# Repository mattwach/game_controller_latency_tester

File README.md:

# game_controller_latency_tester

This project provides a (couple of) hardware designs for interfacing a game
controller to a Raspberry PI (or similar) and automatically measuring the input
latency added by the controller.

## What is input latency?

The "input latency" I'm referring to in this document is the amount of time
that passes between a button being pressed on the controller and application
(game) receiving the event.

This is the sum of all of the following:

   1. The game controller hardware signaling that the button is pressed
      (very fast)
   2. The game controller firmware processing this signal into a USB or
      bluetooth message (varies)
   3. The Raspberry PI USB/bluetooth hardware receiving the message and notifying the
      OS (usually fast)
   4. The Raspberry PI OS handling the message and passing it forward to
      the application (usually fast)

> "button" could also mean deflecting a stick.

## Raspberry PI verses Microcontroller Test Setup

Some setups, such as [this one](https://inputlag.science/controller/methodology)
use microcontroller hardware to handle #1, #3 and #4.  This project uses a
Raspberry PI instead.

One reason to use a microcontroller is more control over the environment.  A
Raspberry PI running Linux could get interrupted in the middle of a measurement
which would unfairly penalize the result.  That said, the PI has many
advantages as well:

   1. Even though the Raspberry PI *could* get interrupted, it's fairly simple
      to create a environment where this is not likely to happen.  For example
      you could run without a graphical environment or any services.  My own
      tests didn't even bother being careful with this and still got similar
      results as the [microcontroller version](https://inputlag.science/controller/methodology)
      testing the < 1ms [GP2040](https://github.com/FeralAI/GP2040) firmware.
   2. The Raspberry PI could be argued a more relevant test in some respects
      as it's using the same path that [RetroPie](https://retropie.org.uk/) would use.
   3. Supporting different configurations is much easier with Raspberry PI.
      For example, testing a bluetooth-based controller generally requires no
      additional hardware or setup.

## Other hardware options.

If Raspberry PI's are still hard to find, there are many alternative options.
The needed requirements are GPIO support and USB.  You *could* use a generic
PC with a USB to GPIO converter to send the needed trigger signals.  Something
like [this](https://www.adafruit.com/product/2264) or make-your-own with a PI Pico.

> Not using a Raspberry pi will likely require some tweaks to the
> source code provided in this project.

So in the text below, you can replace "Raspberry PI" with whatever you hapen to be using.

## Process Overview

   1. The Raspberry PI toggles a GPIO and notes the current time in microsecond
      resolution.
   2. The GPIO signals the game controller to sense that a button was pressed (or
      a stick was deflected)
   3. The controller sends a corresponding USB/Bluetooth message back to the
      Raspberry PI.
   4. Upon receiving the USB/Bluetooth message, the Raspberry PI notes how much
      time has passed since sending the GPIO

1-4 repeats many time (1000 or more) to build up statistics.

## Test Pattern

One test pattern would be to toggle the GPIOs very fast, like 1000 times per
second.  But since no human player could ever do this, it could be argued that
poor results in these setups might not be represent a real-world experience.

The test programs in this project try to set up a more "real world" situation
but toggling two GPIO channels at 10Hz (or 20 inputs per second).  The way this
is implemented is to toggle GPIO1 every 100ms and GPIO2 every 98ms.  This
creates a pattern that looks like this:

The game controller thus has to sometimes handle button being pressed at the
same time as could sometimes happen in real use.

## Interpreting the results

The image above shows output statistics from `simple_latency_test` and the
[GP2040](https://github.com/FeralAI/GP2040) firmware, which has excellent
performance. 

The reported statistics will be as follows:

   * Median Latency: The "middle" latency value where half of the samples are
     larger and half of them are smaller.
   * Standard Deviation: A measure of latency variance.
   * 90% latency: A pessimistic-but-reasonable way to think about the latency
     It basically says that 90% of the time, you'll see less latency than the
     reported number.

### What is "bad" latency?

At 60 Hz, a video frame is (around 16ms).  So if your controller latency is > 16ms, then you will lose a frame due to the controller every time.  If your
latency is 8ms, you will lose a frame about half the time, and so on.

As far as how important a missed frame is, I invite you to draw your own
conclusions.  But here are some sources:

[This reaction time test](https://humanbenchmark.com/tests/reactiontime) shows
humans to be around 200ms on average.

But there is more to gaming that pure reaction.  Most games offer "cues" or
"tells" that are followed by predictable patterns.  Some games are fully
predictable, like playing a song.  When events can be predicted and tracked, it
becomes less about reaction time and more about "temporal precision".
[This particular study](https://jov.arvojournals.org/article.aspx?articleid=2213289)
measured temporal precision at just 6ms for some activities.

So it depends on many things but the studies above suggset there are cases
where low latency "matters" in terms of giving a player an additional advantage
at some games.

## Raspberry PI to Game Controller Interface Hardware

Let's start with the most straight-forward hardware approach. You *could* directly
connect a PI GPIO to a controller and in many cases it will work, but
there are risks:

   1. The Raspberry PI is 3.3V, the controller might be something different, such
      as 5V.  This voltage mismatch could damage the GPIO hardware of the PI.
   2. Connecting the PI to some unknown input could easily lead to situations
      where the PI is trying to power a ground connection to 3.3V or
      "current sink" a powered connection to ground.  These situations can
      lead to the controller and/or PI getting damaged.

Thus I suggest using protection circuitry to keep the PI and controller
isolated from each other and reduce the risks of damage.  I present two
protection designs: optocoupler based, and NFET based.

### NFET Design

[Playground Link](http://www.falstad.com/circuit/circuitjs.html?ctz=CQAgjCAMB0l3BWcMBMcUHYMGZIA4UA2ATmIxAUgoqoQFMBaMMAKACURjCRMUQAWPDwx8qVflWzRsUWTAQsA5uEKSEfMKoFw5LAE4hs6w8f6F+J0TzQsA7gPM88QsxaOiWAZ07deKqn5UEABmAIYANp50+oaQFn64bsZB8HB2sfEilsIe9onZ7tmQLABGFFlgmDzY3PwoMsU1QgjEGlotfFy6TRSt2R3aYlAs2Bi0fZrijpPg3WO9fIUI-EkaugAeAmYCYLTLOzLxFgAudJ7HADqeAMYAlnrXAK63xyyb-MQyYAQUhOTfSAsmhAJUex2OAHsAHYAfQADrcoW8BBhuNgqggSIZcAIVCBbPc6OEzp4YYooQATdggHDcPBUWmGKziWhyKDQBQGRn0mk1fyySjwdKMmYDGbFMp-PiOPBgYjgYgWYqbEgQb50lBqvDyo74wkUq6g8HQljBHa+LKuHJM8Ac9mQFAxQp+fjAwLINKbTUQQjfbHSzW4lAWACqAGUAEJXOEQ2x0PSlBV8D5o7DywhEYb2FCYhbgSp54ocHPcAYlhxK2QSahDeQsABuNOMqiEGGM6iEQ2rSFrHMTf3IlCQBAshCMWab0vwIEIuZbwxVnxnOII3DHhx4VAJeiJJMNYMhSK57ZQQlnpdPAtS6StMyt5eKBitSxWRWsyoEo2XtCx66DW8JYlPE8aNY3jG8unnCQqHnCUBEDIdfjPcdikbFMZ2ndCOzZbs2TrewsMvaCKEvD8iP4L5HBWWo8TYUJPDhEp4z0ABPK4AAVbiuABxdiAEkAHlEzAQ4PnAPByHqeVinsGYEjia0ZIybIZkKYogA)

The NFET design has the advantage of easier hookup and faster operation.  The
disadvantage is that it will only work with ["pull up
resistor"](https://learn.sparkfun.com/tutorials/pull-up-resistors/all) style
buttons. If you unknowingly hook it to something else by mistake, no
damage will occur but the test will not be able to execute.  Pullup
configurations are more commonly used in design but some designs may have
reasons (or arbitrarily) decided to implement their buttons dfferently.

Another advantage of the FET, assumed pull up configuration is that the USB
cable (on USB controllers) can be used as the ground connection for the
test - this simplifies wiring and eliminates some types of wiring errors.

### Opcocoupler Design

[Playground Link](http://www.falstad.com/circuit/circuitjs.html?ctz=CQAgjCAMB0l3BWcMBMcUHYMGZIA4UA2ATmIxAUgoqoQFMBaMMAKACVxCq09wwUQPKMIAsVbNGzCqMBCwDm4DIUF5eYZSGzYVMlgHcQI4ipRijJ1b0gsAzp275B5oVQgAzAIYAbW3RYARiBc5IQighgQOno6vIRmgk7x4WAi4TGEcQkoasEJ2rpQLNgYVMmJvMamThAxpXnhObwImk3g0iwAHkYYvNgiKgh4Kv3ERs4gAC50tpMAOrYAxgCWAE6LAK7Lk10UKEjMzaTgKBApKgEbk5MA9gB2APoADst3u5S8RFJcEEQq5yB9Gs6N4ZrYHvI7gATFirLQ6CpGOCI8S4FgANxAyma-CxmSM2AEMiR1GJskCwWIUjEYzw5gQ2DGNkM2IJAkIGAEIkJRW6JCkDPCeG0FBK4zQICeG283ihN30dwWl2u91heJx7M5FFxtHgNjhVSsFFauVRNm6lAgguC2GaYsaVFWdHRdFWfihCye8tdBgoXG1XLCAaKQREeCQNJtAgZTIxfqo3Oj-oQOtEtGkUGgckMCH9iaMQfzNjE5DEjkqliErEMZecCeRbWZSO4uQKRqb2AQXJ5+3+PJsmM70dxQ7ZGfpGfJQUwpcgYxECRjRUMo5TAl7wfNgipovC-XIDNLiUl3tWas55YaKJo8F2hEIUTAVCwSGwYGpx6lMo2TyVV1ubwshKbTlI2FJhAc4ZYsQAhvkgA5YsBuQXte9aktIWYKOqwZ4Mia4dIoKFtBgXbtkUiiriOdKbuR8ZjggMFjnoK4Im0GimKavpmJebauLsJFaDgggjpoAJsJ4thPAErqrAAngsAAKACSCwAOLKQA8hS3FaNR8RKLGQA)

The optocoupler based design will work with either pull up or pull down
configuratons, but you need to known which way the current flows through the
button and connect two wires per button. Getting any of this wrong
should not do any damage, but the test will fail to execute.  Optocouplers
are also quite a bit slower than FETs.  The one I had on-hand took around 2us
to activate and 100+us to turn itself off.  You can get faster ones, but need
to look at the datasheet when you pick one.  In comparison, FET's just take
a handful of ns to turn on/off.  

Going forward, I'll assume we are going with the NFET design.  If you need
the optocoupler one, then your hardware build will be different but the
software you run will be the same.

## Board Design

In the [latency_schematic/](latency_schematic) directory, I put together a
schematic of the NFET design:

As well as a PCB layout that you can hand-wire, CNC cut, chemical etch or send
to a fab.

Here is my finished hardware:

## Hardware Hookup

Here is the hardware connected to a Mayflash F500 arcade stick:

One wire for each GPIO.  There is no need to connect a ground wire in this case
because there is a ground connection from the USB connection.  If this were
a wireless controller, then the additional ground wire would need to be
connected.

## Software Tools

Most of the tools you will build as a part of this project.  The process is
to type

    make

The standard Raspberry PI image should already contain the dependencies that
you will need.

### jstest-gtk

This is a commonly-availabe tool.  e.g. in Ubuntu you can just say

    sudo apt install jstest-gtk
    
to install the software.  This software can be used to verify that your
controller is connected and working.  It can also tell you the device number
(which is often /dev/input/js0 if you only have one connected).

### toggle_test

This tool was built when you executed `make`.  You run it like this

    ./toggle_test

The test simply toggles GPIO6 and GPIO22 every second.  If you have jstest-gtk running
and the hardware all hooked up, you will ideally see the software reporting that
buttons are being pressed.

### joystick_events

This utility is a less-advanced commandline variant of jstest-gtk.  You may not
need to run it at all but it can be useful as an alternative tool.  Usage is
simple:

    ./joystick_events

The tool assumes the device is `/dev/input/js0`.  This can be changed in `joystick_events.c`

### simple_latency_test

This is a single-channel version of the test that only uses GPIO22.  In my
testing, it gives the lowest latency numbers, especially in standard deviation.
It works by toggling a gpio, waiting for the response, then toggling another
one.  So it's a bit easier on the firmware than `multichannel_latency_test`.
Usage is again simple:

    ./simple_latency_test

### multichannel_latency_test

This version uses GPIO6 and GPIO22, toggling them in overlapping ways.  Usage
is again simple:

    ./multichannel_latency_test

## Taking It Further - Video Latency

With additional work, we can measure the latency from pushing a button all the
way to seeing something happen on the screen.  This takes the current latency
sources and adds the video pipeline and any processing the monitor may be doing.

> I'll just say that if you are connected to a TV, make sure it's in "game mode"
> to potentially avoid hundreds of additional ms of latency!

I didn't set this up, but here is a basic recipe for those who might want to:

1. You modify the software tools to draw a white rectangle on an otherwise
   black screen.
2. You use either a phototransistor or photodiode, pressed up close to the
   screen so that it can detect the change without picking up other
   light.
3. The phototransistor/photodiode drives a GPIO on the Rasperry PI.  The
   software monitors that GPIO to collect latency timing information.

Here is a basic phototransistor circuit that would be **combined** with one
of the circuits above (since you still want the ability to trigger the
buttons):

[playground link](http://www.falstad.com/circuit/circuitjs.html?ctz=CQAgjCAMB0l3BWcMBMcUHYMGZIA4UA2ATmIxAUgoqoQFMBaMMAKABcRCUAWEFPPJwwo+AqOBANssYmGwps2BGB7CwxKNDR5CGbsX0JC3IwgTZkVACZ0AZgEMArgBs2LAEohu3Qf0Hc4UUEqKgCJEM0EFgBnCm8gzh4EqggHZ2i6DxA8eXB+bOJCPODxMOkLCJgogHMhEVxeXXqEERCWMD1E3nURJuKJMHgQ6CR3OmiAS2i2ewA7AGNMgCc68EIqPsxWvjQWbEJBTeFsvCot8UgWAHds3JVDpPuoFhWEeL8vH2TLS4AjEGweF4iiKXAgCnIfxAOCKhRAhUEilaLAAHtD9ACFNlCEh5EVeGgQO57NEAA6-OhLJYATwAOtEAAoASVRALh8g063quQJVAAyhMALYuexsOhWekAGQm1QAFmx6XyAPaOJaLVkYYx8QhFPCUbUabpFZWCuj0gDizIA8iwgA)

The potentiometer is used to change the sensitivity of the circuit.  Again, this
is just a starting point to give you some terms to search for.  Building up the
circuit above (or an alternate example you find) and testing it on a breadboard
is recommended before building anying permanent.

If you go with a photodiode, the circuit will be a bit different.  I also found
some [photodiode modules on Amazon](https://www.amazon.com/uxcell-Photosensitive-Terminals-Detection-Photodiode/dp/B07M8WS8TH) that look
easy to use.  Another option to consider.

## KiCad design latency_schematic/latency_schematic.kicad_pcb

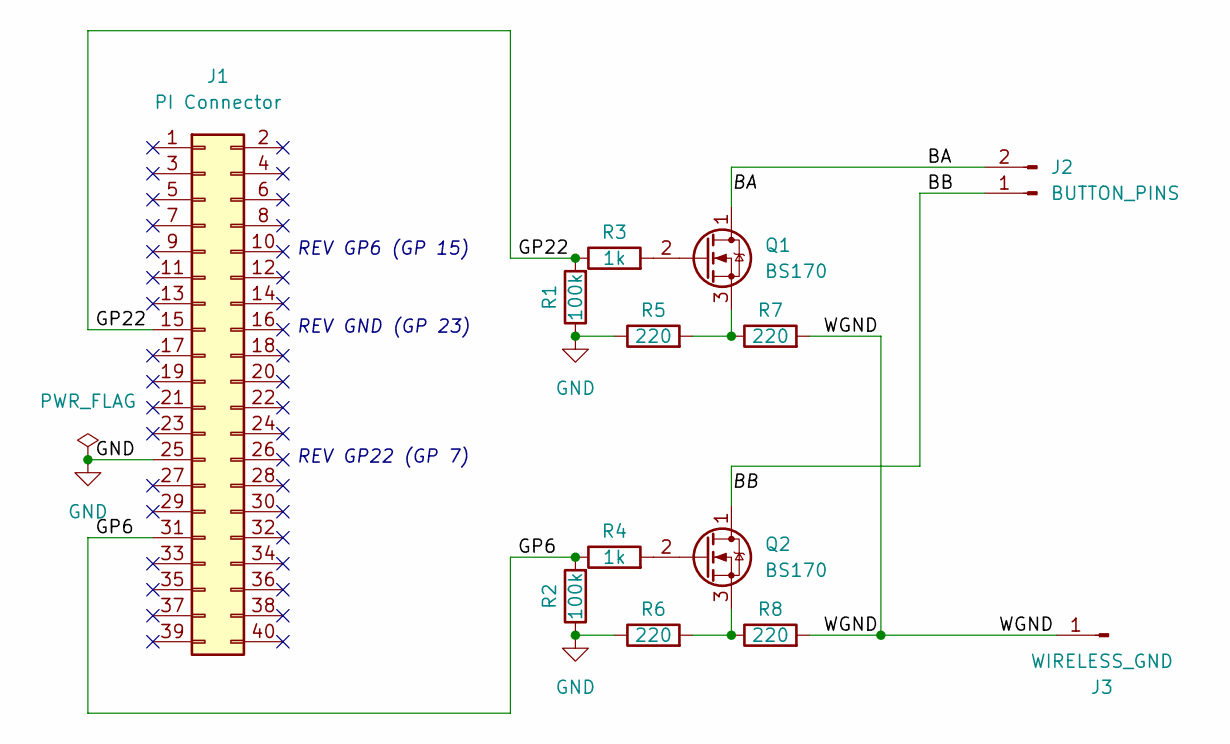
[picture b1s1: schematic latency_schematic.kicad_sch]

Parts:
J1: PI Connector; PinSocket_2x20_P2.54mm_Vertical
J2: BUTTON_PINS; PinSocket_1x02_P2.54mm_Vertical
J3: WIRELESS_GND; PinSocket_1x01_P2.54mm_Vertical
Q1, Q2: BS170; TO-92_Inline_Wide
R1, R2: 100k; R_Axial_DIN0207_L6.3mm_D2.5mm_P10.16mm_Horizontal
R3, R4: 1k; R_Axial_DIN0207_L6.3mm_D2.5mm_P10.16mm_Horizontal
R5, R6, R7, R8: 220; R_Axial_DIN0207_L6.3mm_D2.5mm_P10.16mm_Horizontal

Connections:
/BA: J2.2, Q1.1 (D)
/BB: J2.1, Q2.1 (D)
/GP6: J1.31, R2.2, R4.1
/GP22: J1.15, R1.2, R3.1
/WGND: J3.1, R7.2, R8.2
GND: J1.25, R1.1, R2.1, R5.1, R6.1
unnamed: Q1.2 (G), R3.2
unnamed: Q1.3 (S), R5.2, R7.1
unnamed: Q2.2 (G), R4.2
unnamed: Q2.3 (S), R6.2, R8.1

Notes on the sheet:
REV GP22 (GP 7)
REV GND (GP 23)
REV GP6 (GP 15)

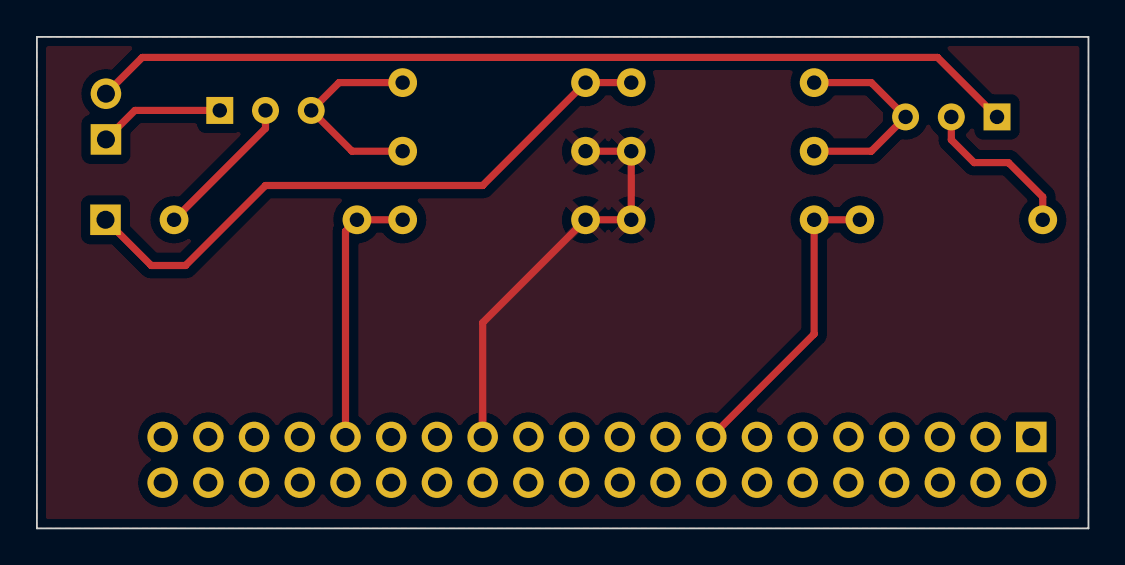
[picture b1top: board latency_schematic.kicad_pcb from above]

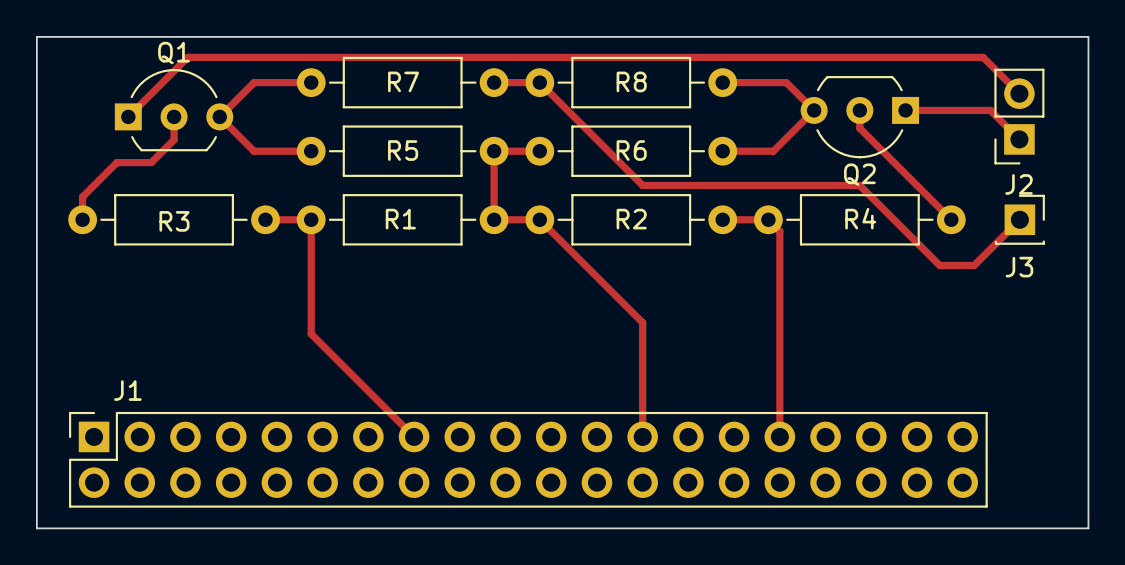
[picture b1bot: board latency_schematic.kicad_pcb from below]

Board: 2 copper layers, 58.4 x 27.3 mm, 13 parts (13 on the bottom side), 10 nets.

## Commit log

2023-02-26 Added basic files
2023-02-27 Working on README file
2023-03-08 README updates
2023-03-08 Added gpio pattern image
2023-03-10 Added images and falstad links
2023-03-11 Added more images
2023-03-16 Added some phototransistor information
2023-03-16 Typo fixes
2023-03-23 Some wording updates
2023-03-25 MOre readme updates
